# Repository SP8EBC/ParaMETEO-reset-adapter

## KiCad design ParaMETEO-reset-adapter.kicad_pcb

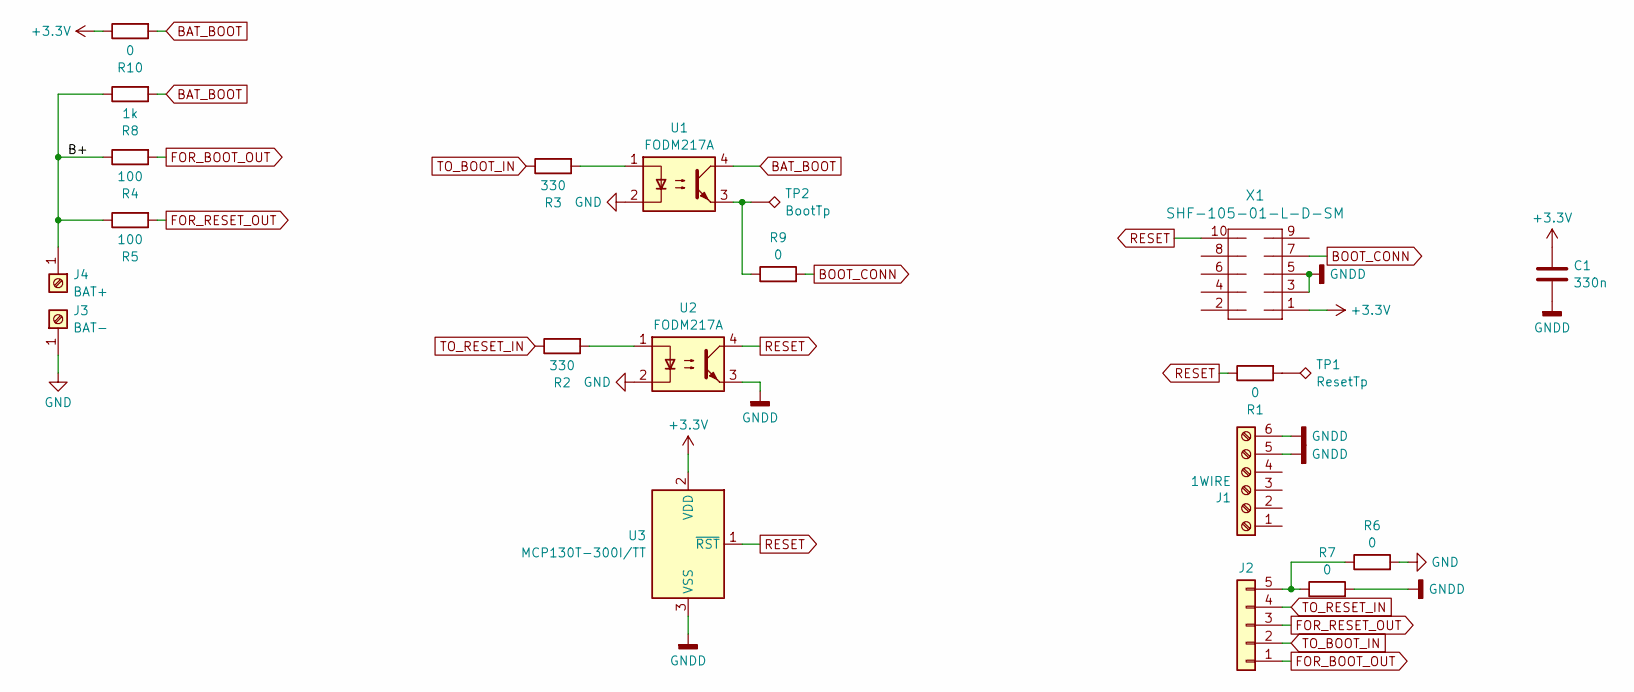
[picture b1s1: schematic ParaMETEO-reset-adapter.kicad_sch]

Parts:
C1: 330n; C_0805_2012Metric_Pad1.18x1.45mm_HandSolder
J1: 1WIRE; 1830870
J2: Screw_Terminal_01x06; PinHeader_1x05_P2.54mm_Vertical
J3: BAT-; SolderWire-1.5sqmm_1x01_D1.7mm_OD3.9mm
J4: BAT+; SolderWire-1.5sqmm_1x01_D1.7mm_OD3.9mm
R1, R6, R7, R9, R10: 0; R_0805_2012Metric_Pad1.20x1.40mm_HandSolder
R2, R3: 330; R_0805_2012Metric_Pad1.20x1.40mm_HandSolder
R4, R5: 100; R_0805_2012Metric_Pad1.20x1.40mm_HandSolder
R8: 1k; R_0805_2012Metric_Pad1.20x1.40mm_HandSolder
TP1: ResetTp; TestPoint_Plated_Hole_D2.0mm
TP2: BootTp; TestPoint_Plated_Hole_D2.0mm
U1, U2: FODM217A; SOP-4_4.4x2.6mm_P1.27mm
U3: MCP130T-300I/TT; SOT-23
X1: SHF-105-01-L-D-SM; PHB_1MM27_2X05_SNS

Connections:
+3.3V: C1.1, R10.1, U3.2 (VDD), X1.1
/B+: J4.1, R4.1, R5.1, R8.1
BAT_BOOT: R8.2, R10.2, U1.4
BOOT_CONN: R9.2, X1.7
FOR_BOOT_OUT: J2.1, R4.2
FOR_RESET_OUT: J2.3, R5.2
GND: J3.1, R6.2, U1.2, U2.2
GNDD: C1.2, J1.5, J1.6, R7.2, U2.3, U3.3 (VSS), X1.3, X1.5
unnamed: J2.5, R6.1, R7.1
unnamed: R1.2, TP1.1
unnamed: R2.2, U2.1
unnamed: R3.2, U1.1
unnamed: R9.1, TP2.1, U1.3
RESET: R1.1, U2.4, U3.1 (~RST), X1.10
TO_BOOT_IN: J2.2, R3.1
TO_RESET_IN: J2.4, R2.1

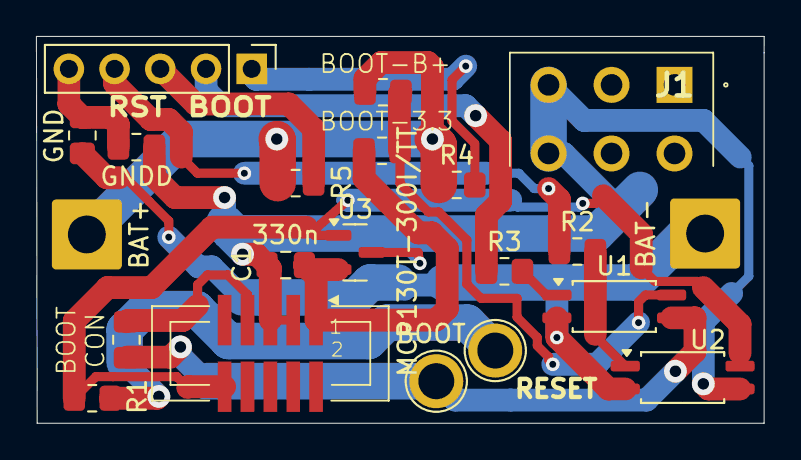
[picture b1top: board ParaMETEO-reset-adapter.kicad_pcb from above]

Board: 2 copper layers, 40.4 x 21.5 mm, 21 parts (0 on the bottom side), 16 nets.

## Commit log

2025-11-26 first
2025-11-28 final version pushed do jblpcb
